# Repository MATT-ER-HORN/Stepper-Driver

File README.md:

# Stepper-Driver
Heinlab ESP32 Stepper Driver

Gerbers and firmware coming soon

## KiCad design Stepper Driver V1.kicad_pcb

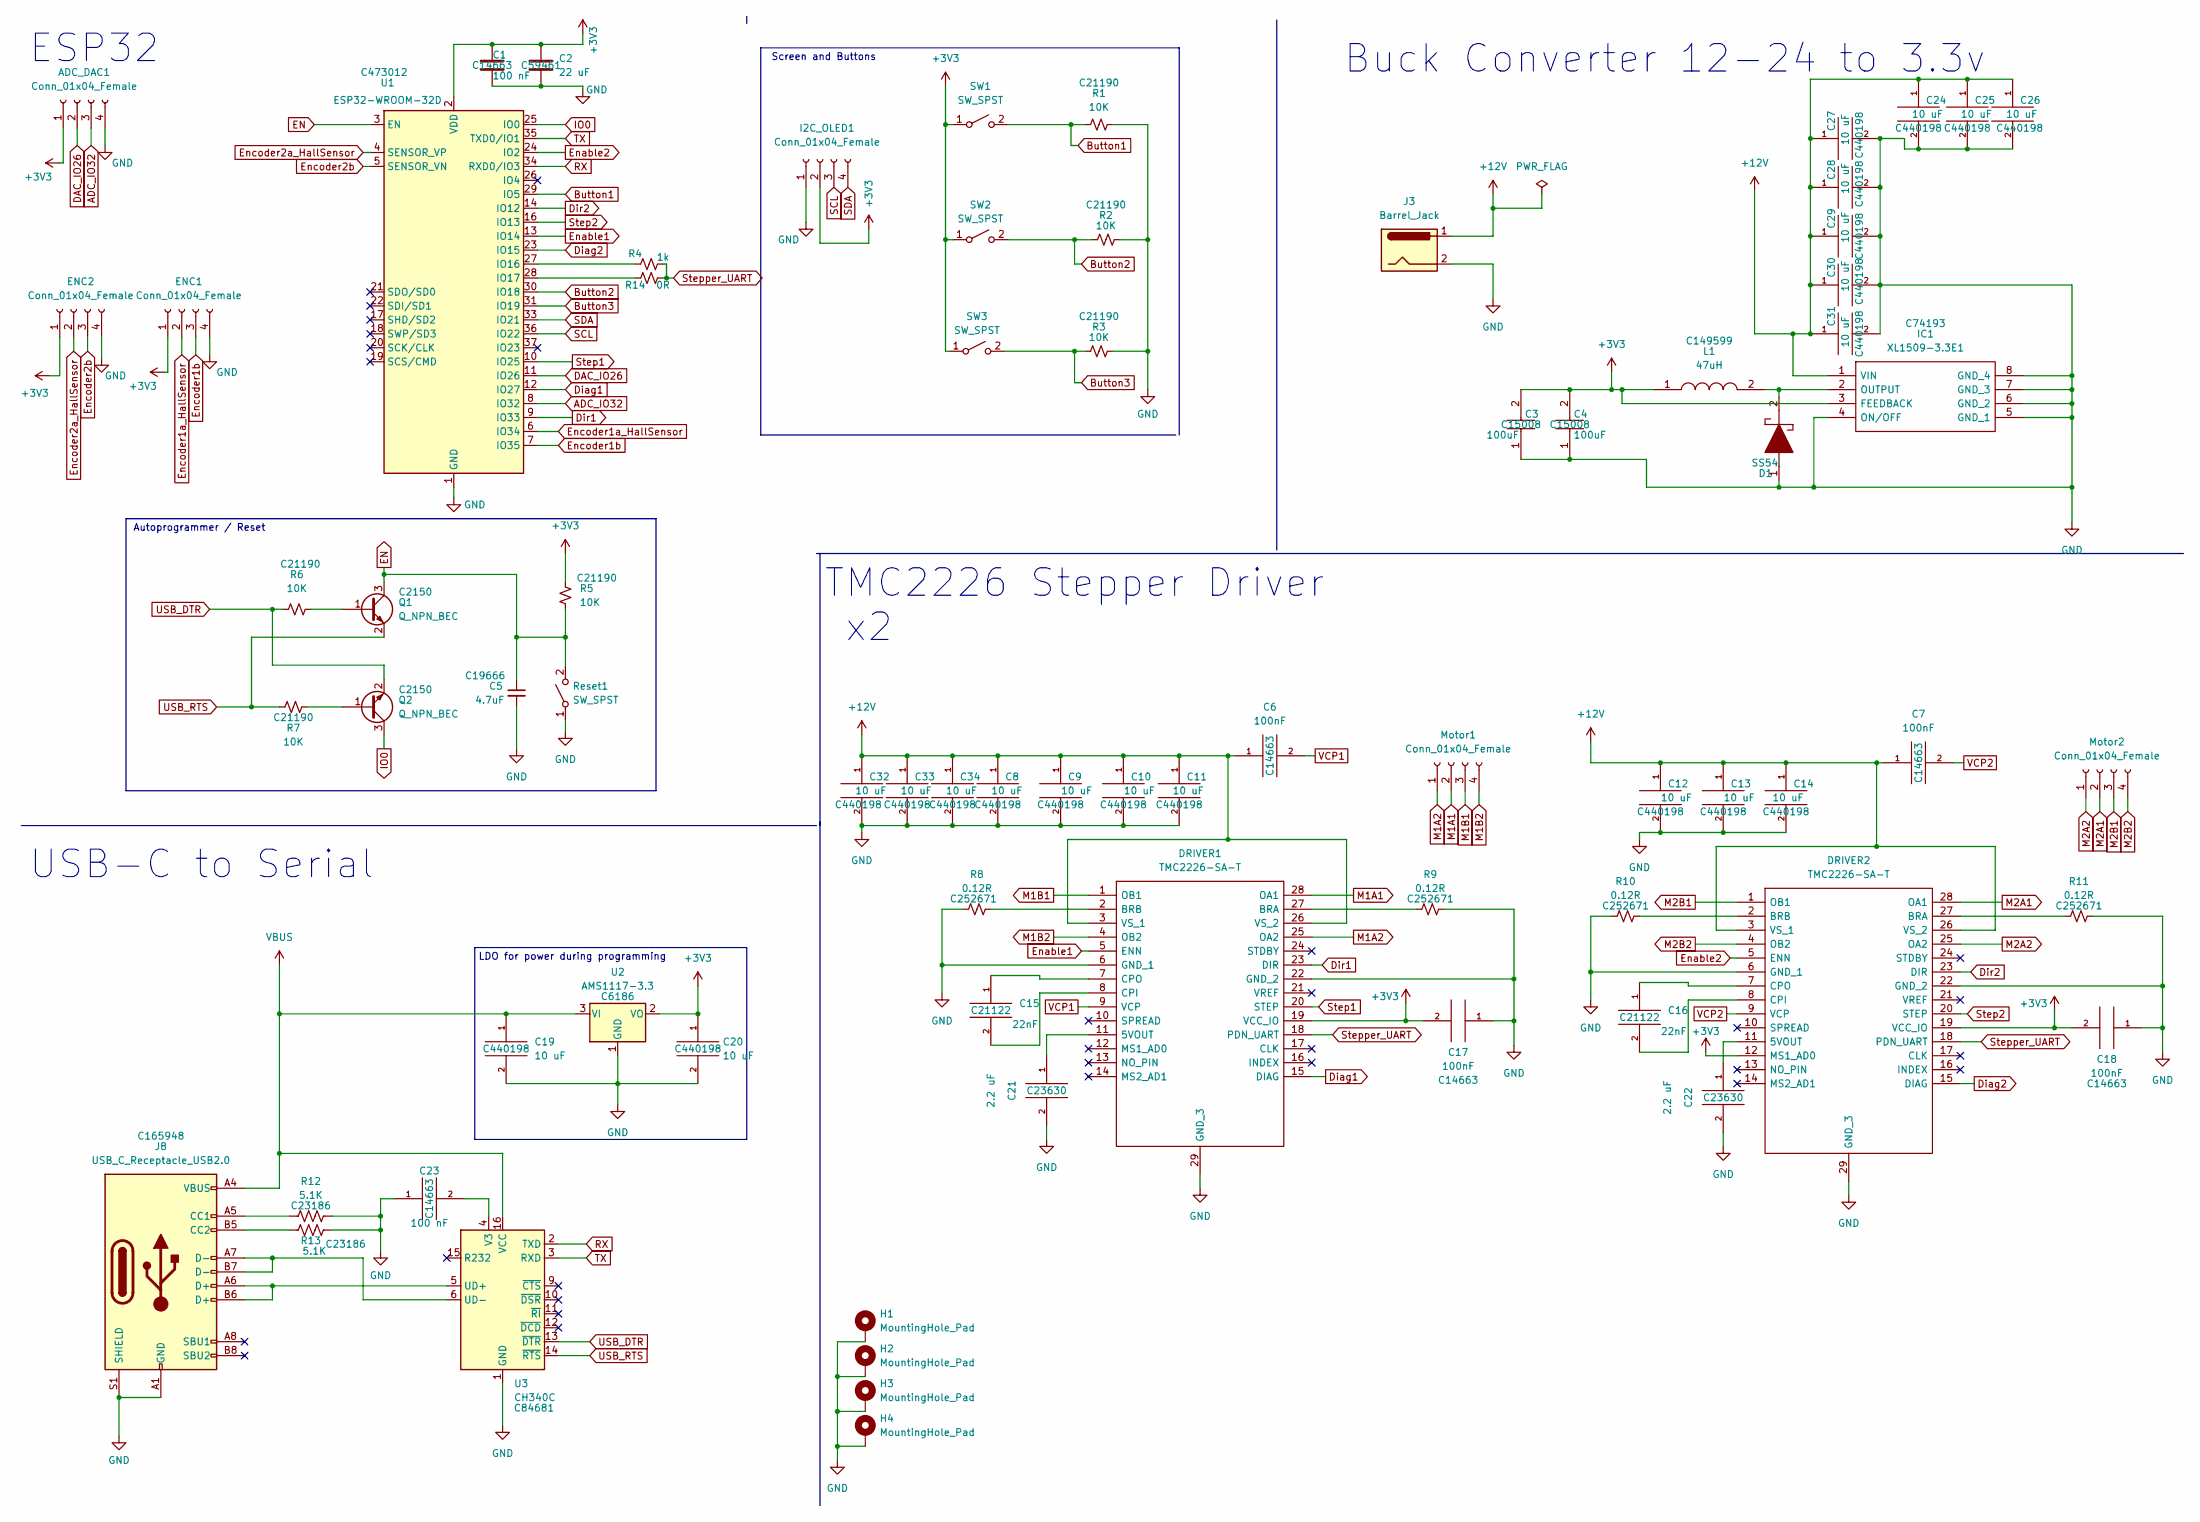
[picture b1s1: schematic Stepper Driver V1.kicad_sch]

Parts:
ADC_DAC1: Conn_01x04_Female; JST_XH_B4B-XH-A_1x04_P2.50mm_Vertical
C1, C23: 100 nF; C_0603_1608Metric; MFR.Part # CC0603KRX7R9BB104; JLCPCB Part # C14663
C2: 22 uF; C_0603_1608Metric; MFR.Part # CL10A226MQ8NRNC; JLCPCB Part # C59461
C3, C4: 100uF; C_1206_3216Metric; Mouser Part Number 187-CL31A107MQHNNNE
C5: 4.7uF; C_0603_1608Metric; MFR.Part # CL10A475KO8NNNC; JLCPCB Part # C19666
C6, C7, C17, C18: 100nF; C_0603_1608Metric; MFR.Part # CC0603KRX7R9BB104; JLCPCB Part # C14663
C8, C9, C10, C11, C12, C13, C14, C19, C20, C24, C25, C26, C27, C28, C29, C30, C31, C32, C33, C34: 10 uF; C_1206_3216Metric; MFR.Part # GRM21BR61H106KE43L; JLCPCB Part # C440198
C15, C16: 22nF; C_0603_1608Metric; MFR.Part # CL10B223KB8NNNC; JLCPCB Part # C21122
C21, C22: 2.2 uF; C_0603_1608Metric; MFR.Part # CL10A225KO8NNNC; JLCPCB Part # C23630
D1: SS54; DIONM7959X262N; Manufacturer_Part_Number SS54; JLCPCB Part # C22452
DRIVER1, DRIVER2: TMC2226-SA-T; Mouser Part Number 700-TMC2226-SA-T
ENC1, ENC2: Conn_01x04_Female; JST_XH_B4B-XH-A_1x04_P2.50mm_Vertical
H1, H2, H3, H4: MountingHole_Pad; MountingHole_3.2mm_M3_Pad_Via
I2C_OLED1: Conn_01x04_Female; JST_XH_B4B-XH-A_1x04_P2.50mm_Vertical
IC1: XL1509-3.3E1; SOIC127P600X175-8N; Manufacturer_Part_Number XL1509-3.3E1; JLCPCB Part # C74193
J3: Barrel_Jack; BarrelJack_GCT_DCJ200-10-A_Horizontal
J8: USB_C_Receptacle_USB2.0; USB_C_Receptacle_HRO_TYPE-C-31-M-12; MFR.Part # TYPE-C-31-M-12; JLCPCB Part # C165948
L1: 47uH; INDPM115100X400N; Manufacturer_Part_Number SMMS0650-470M; JLCPCB Part # C149599
Motor1, Motor2: Conn_01x04_Female; JST_XH_B4B-XH-A_1x04_P2.50mm_Vertical
Q1, Q2: Q_NPN_BEC; TSOT-23; MFR.Part # SS8050; JLCPCB Part # C2150
R1, R2, R3, R5, R6, R7: 10K; R_0603_1608Metric; MFR.Part # 0603WAF1001T5E; JLCPCB Part # C21190
R4: 1k; R_0603_1608Metric; MFR.Part # 0603WAF1001T5E; JLCPCB Part # C21190
R8, R9, R10, R11: 0.12R; R_2512_6332Metric; MFR.Part # MA251220FR120FZ; JLCPCB Part # C252671
R12, R13: 5.1K; R_0603_1608Metric; MFR.Part # 0603WAF5101T5E; JLCPCB Part # C23186
R14: 0R; R_0603_1608Metric; MFR.Part # 0603WAF0000T5E; JLCPCB Part # C21189
Reset1: SW_SPST; SW_SPST_TL3305A
SW1, SW2, SW3: SW_SPST; SW_SPST_TL3305A
U1: ESP32-WROOM-32D; ESP32-WROOM-32; MFR.Part # ESP32-WROOM-32D; JLCPCB Part # C473012
U2: AMS1117-3.3; SOT-223-3_TabPin2; MFR.Part # AMS1117-3.3; JLCPCB Part # C6186
U3: CH340C; SOIC-16_3.9x9.9mm_P1.27mm; MFR.Part # CH340C; JLCPCB Part # C84681

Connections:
+3V3: ADC_DAC1.1, C1.1, C2.1, C3.2, C4.2, C17.2, C18.2, C20.1, DRIVER1.19 (VCC_IO), DRIVER2.12 (MS1_AD0), DRIVER2.19 (VCC_IO), ENC1.1, ENC2.1, I2C_OLED1.2, IC1.3 (FEEDBACK), L1.1, R5.1, SW1.1 (A), SW2.1 (A), SW3.1 (A), U1.2 (VDD), U2.2 (VO)
+12V: C6.1, C7.1, C8.1, C9.1, C10.1, C11.1, C12.1, C13.1, C14.1, C24.1, C25.1, C26.1, C27.1, C28.1, C29.1, C30.1, C31.1, C32.1, C33.1, C34.1, DRIVER1.3 (VS_1), DRIVER1.26 (VS_2), DRIVER2.3 (VS_1), DRIVER2.26 (VS_2), IC1.1 (VIN), J3.1
ADC_IO32: ADC_DAC1.3, U1.8 (IO32)
Button1: R1.1, SW1.2 (B), U1.29 (IO5)
Button2: R2.1, SW2.2 (B), U1.30 (IO18)
Button3: R3.1, SW3.2 (B), U1.31 (IO19)
DAC_IO26: ADC_DAC1.2, U1.11 (IO26)
Diag1: DRIVER1.15 (DIAG), U1.12 (IO27)
Diag2: DRIVER2.15 (DIAG), U1.23 (IO15)
Dir1: DRIVER1.23 (DIR), U1.9 (IO33)
Dir2: DRIVER2.23 (DIR), U1.14 (IO12)
EN: C5.1, Q1.3 (C), R5.2, Reset1.2 (B), U1.3 (EN)
Enable1: DRIVER1.5 (ENN), U1.13 (IO14)
Enable2: DRIVER2.5 (ENN), U1.24 (IO2)
Encoder1a_HallSensor: ENC1.2, U1.6 (IO34)
Encoder1b: ENC1.3, U1.7 (IO35)
Encoder2a_HallSensor: ENC2.2, U1.4 (SENSOR_VP)
Encoder2b: ENC2.3, U1.5 (SENSOR_VN)
GND: ADC_DAC1.4, C1.2, C2.2, C3.1, C4.1, C5.2, C8.2, C9.2, C10.2, C11.2, C12.2, C13.2, C14.2, C17.1, C18.1, C19.2, C20.2, C21.2, C22.2, C23.1, C24.2, C25.2, C26.2, C27.2, C28.2, C29.2, C30.2, C31.2, C32.2, C33.2, C34.2, D1.1, DRIVER1.6 (GND_1), DRIVER1.22 (GND_2), DRIVER1.29 (GND_3), DRIVER2.6 (GND_1), DRIVER2.22 (GND_2), DRIVER2.29 (GND_3), ENC1.4, ENC2.4, H1.1, H2.1, H3.1, H4.1, I2C_OLED1.1, IC1.4 (ON/OFF), IC1.5 (GND_1), IC1.6 (GND_2), IC1.7 (GND_3), IC1.8 (GND_4), J3.2, J8.A1 (GND), J8.A12 (GND), J8.B1 (GND), J8.B12 (GND), J8.S1 (SHIELD), R1.2, R2.2, R3.2, R8.1, R9.2, R10.1, R11.2, R12.2, R13.2, Reset1.1 (A), U1.1 (GND), U1.15 (GND), U1.38 (GND), U1.39 (GND), U2.1 (GND), U3.1 (GND)
IO0: Q2.3 (C), U1.25 (IO0)
M1A1: DRIVER1.28 (OA1), Motor1.2
M1A2: DRIVER1.25 (OA2), Motor1.1
M1B1: DRIVER1.1 (OB1), Motor1.3
M1B2: DRIVER1.4 (OB2), Motor1.4
M2A1: DRIVER2.28 (OA1), Motor2.2
M2A2: DRIVER2.25 (OA2), Motor2.1
M2B1: DRIVER2.1 (OB1), Motor2.3
M2B2: DRIVER2.4 (OB2), Motor2.4
unnamed: C15.1, DRIVER1.7 (CPO)
unnamed: C15.2, DRIVER1.8 (CPI)
unnamed: C16.1, DRIVER2.7 (CPO)
unnamed: C16.2, DRIVER2.8 (CPI)
unnamed: C21.1, DRIVER1.11 (5VOUT)
unnamed: C22.1, DRIVER2.11 (5VOUT)
unnamed: C23.2, U3.4 (V3)
unnamed: D1.2, IC1.2 (OUTPUT), L1.2
unnamed: DRIVER1.2 (BRB), R8.2
unnamed: DRIVER1.27 (BRA), R9.1
unnamed: DRIVER2.2 (BRB), R10.2
unnamed: DRIVER2.27 (BRA), R11.1
unnamed: J8.A5 (CC1), R12.1
unnamed: J8.A6 (D+), J8.B6 (D+), U3.5 (UD+)
unnamed: J8.A7 (D-), J8.B7 (D-), U3.6 (UD-)
unnamed: J8.B5 (CC2), R13.1
unnamed: Q1.1 (B), R6.1
unnamed: Q2.1 (B), R7.1
unnamed: R4.1, U1.27 (IO16)
unnamed: R14.1, U1.28 (IO17)
RX: U1.34 (RXD0/IO3), U3.2 (TXD)
SCL: I2C_OLED1.3, U1.36 (IO22)
SDA: I2C_OLED1.4, U1.33 (IO21)
Step1: DRIVER1.20 (STEP), U1.10 (IO25)
Step2: DRIVER2.20 (STEP), U1.16 (IO13)
Stepper_UART: DRIVER1.18 (PDN_UART), DRIVER2.18 (PDN_UART), R4.2, R14.2
TX: U1.35 (TXD0/IO1), U3.3 (RXD)
USB_DTR: Q2.2 (E), R6.2, U3.13 (~DTR)
USB_RTS: Q1.2 (E), R7.2, U3.14 (~RTS)
VBUS: C19.1, J8.A4 (VBUS), J8.A9 (VBUS), J8.B4 (VBUS), J8.B9 (VBUS), U2.3 (VI), U3.16 (VCC)
VCP1: C6.2, DRIVER1.9 (VCP)
VCP2: C7.2, DRIVER2.9 (VCP)

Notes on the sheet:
Screen and Buttons
ESP32
Buck Converter 12-24 to 3.3v
USB-C to Serial
LDO for power during programming
Autoprogrammer / Reset
TMC2226 Stepper Driver x2

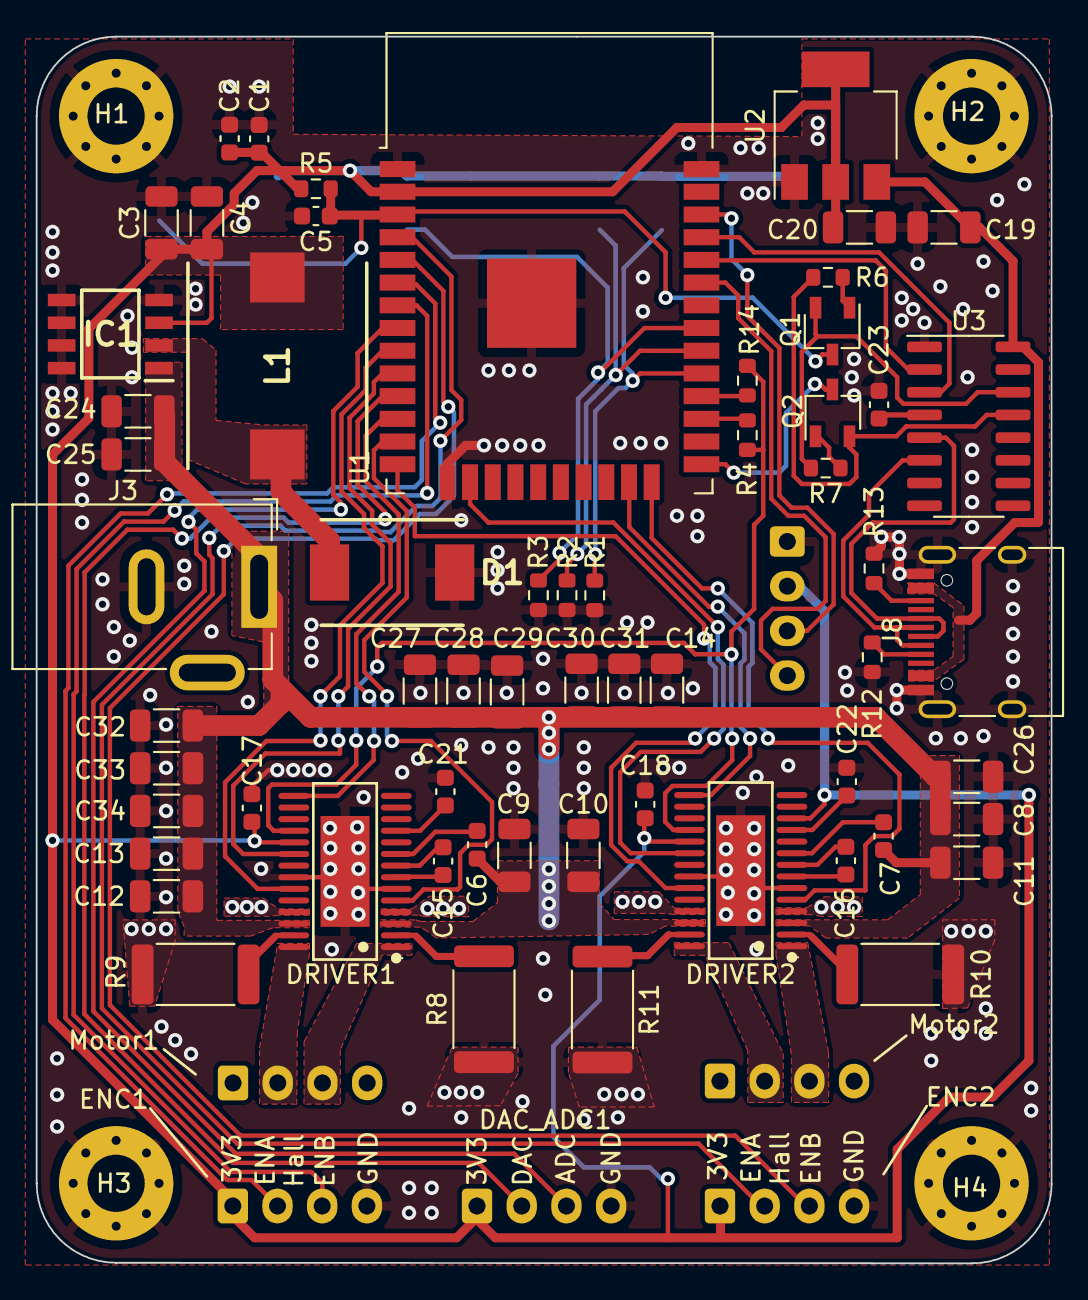
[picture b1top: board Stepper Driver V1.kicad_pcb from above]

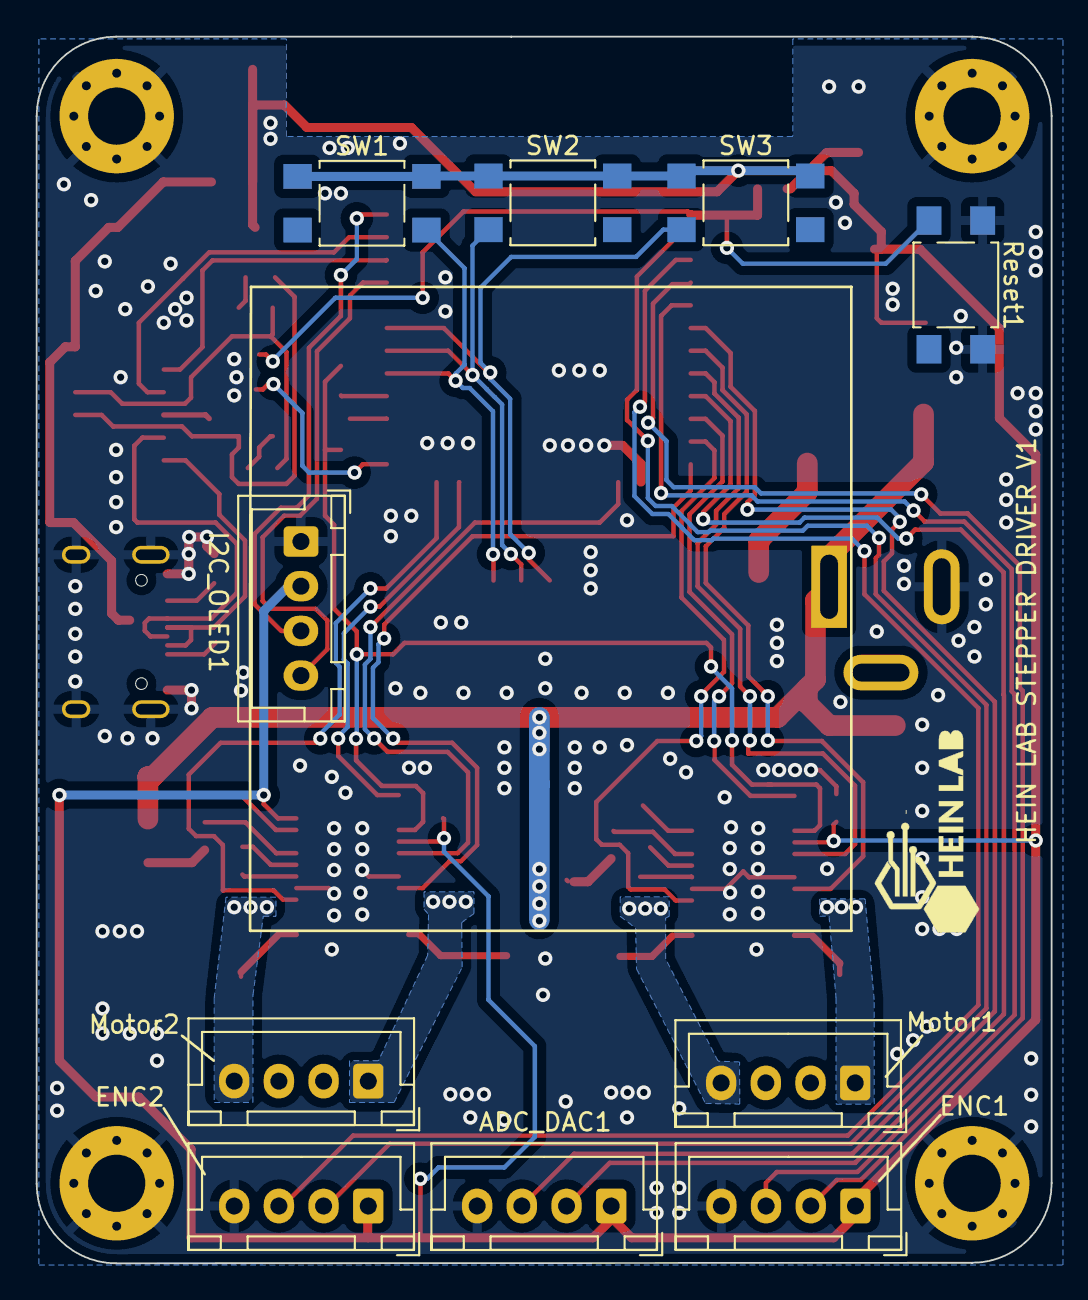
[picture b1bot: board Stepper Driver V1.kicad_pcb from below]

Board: 2 copper layers, 56.8 x 68.6 mm, 74 parts (10 on the bottom side), 60 nets.
